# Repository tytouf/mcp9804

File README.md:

mcp9804
=======

MCP9804 Digital Temperature Sensor

This repository includes:
* an Eagle library to create schematics and PCB with this component in MSOP8 package
* an Arduino library to interface it to an Arduino board.

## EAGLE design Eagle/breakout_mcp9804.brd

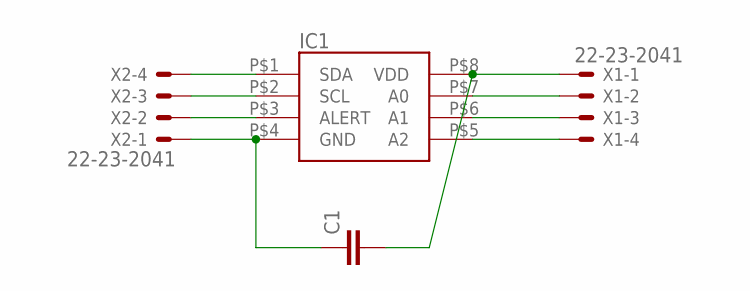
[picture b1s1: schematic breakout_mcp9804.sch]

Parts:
C1: C-EUC1206; C1206
IC1: MPC9804; MSOP-8
X1, X2: 22-23-2041

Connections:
unnamed: IC1.P$1 (SDA), X2.4
unnamed: IC1.P$2 (SCL), X2.3
unnamed: IC1.P$3 (ALERT), X2.2
unnamed: C1.1, IC1.P$4 (GND), X2.1
unnamed: C1.2, IC1.P$8 (VDD), X1.1
unnamed: IC1.P$7 (A0), X1.2
unnamed: IC1.P$6 (A1), X1.3
unnamed: IC1.P$5 (A2), X1.4

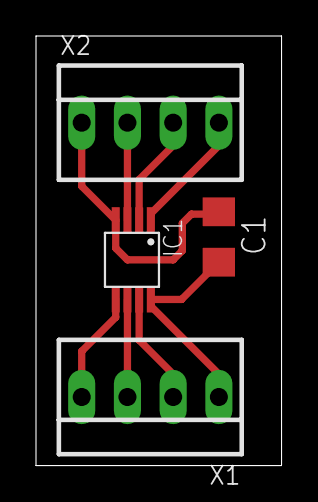
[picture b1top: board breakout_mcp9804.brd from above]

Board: 2 copper layers, 13.6 x 23.9 mm, 4 parts (0 on the bottom side), 8 nets.

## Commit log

2013-03-20 Initial commit with eagle library
2013-03-24 Create Eagle subdirectory
2013-03-24 Initial commit of the Arduino library
    The library can be used to access a MCP9804 sensor connected on
    an Arduino board.
2013-03-24 Fix README file
2013-03-24 Arduino: Add comments on configuration in examples
